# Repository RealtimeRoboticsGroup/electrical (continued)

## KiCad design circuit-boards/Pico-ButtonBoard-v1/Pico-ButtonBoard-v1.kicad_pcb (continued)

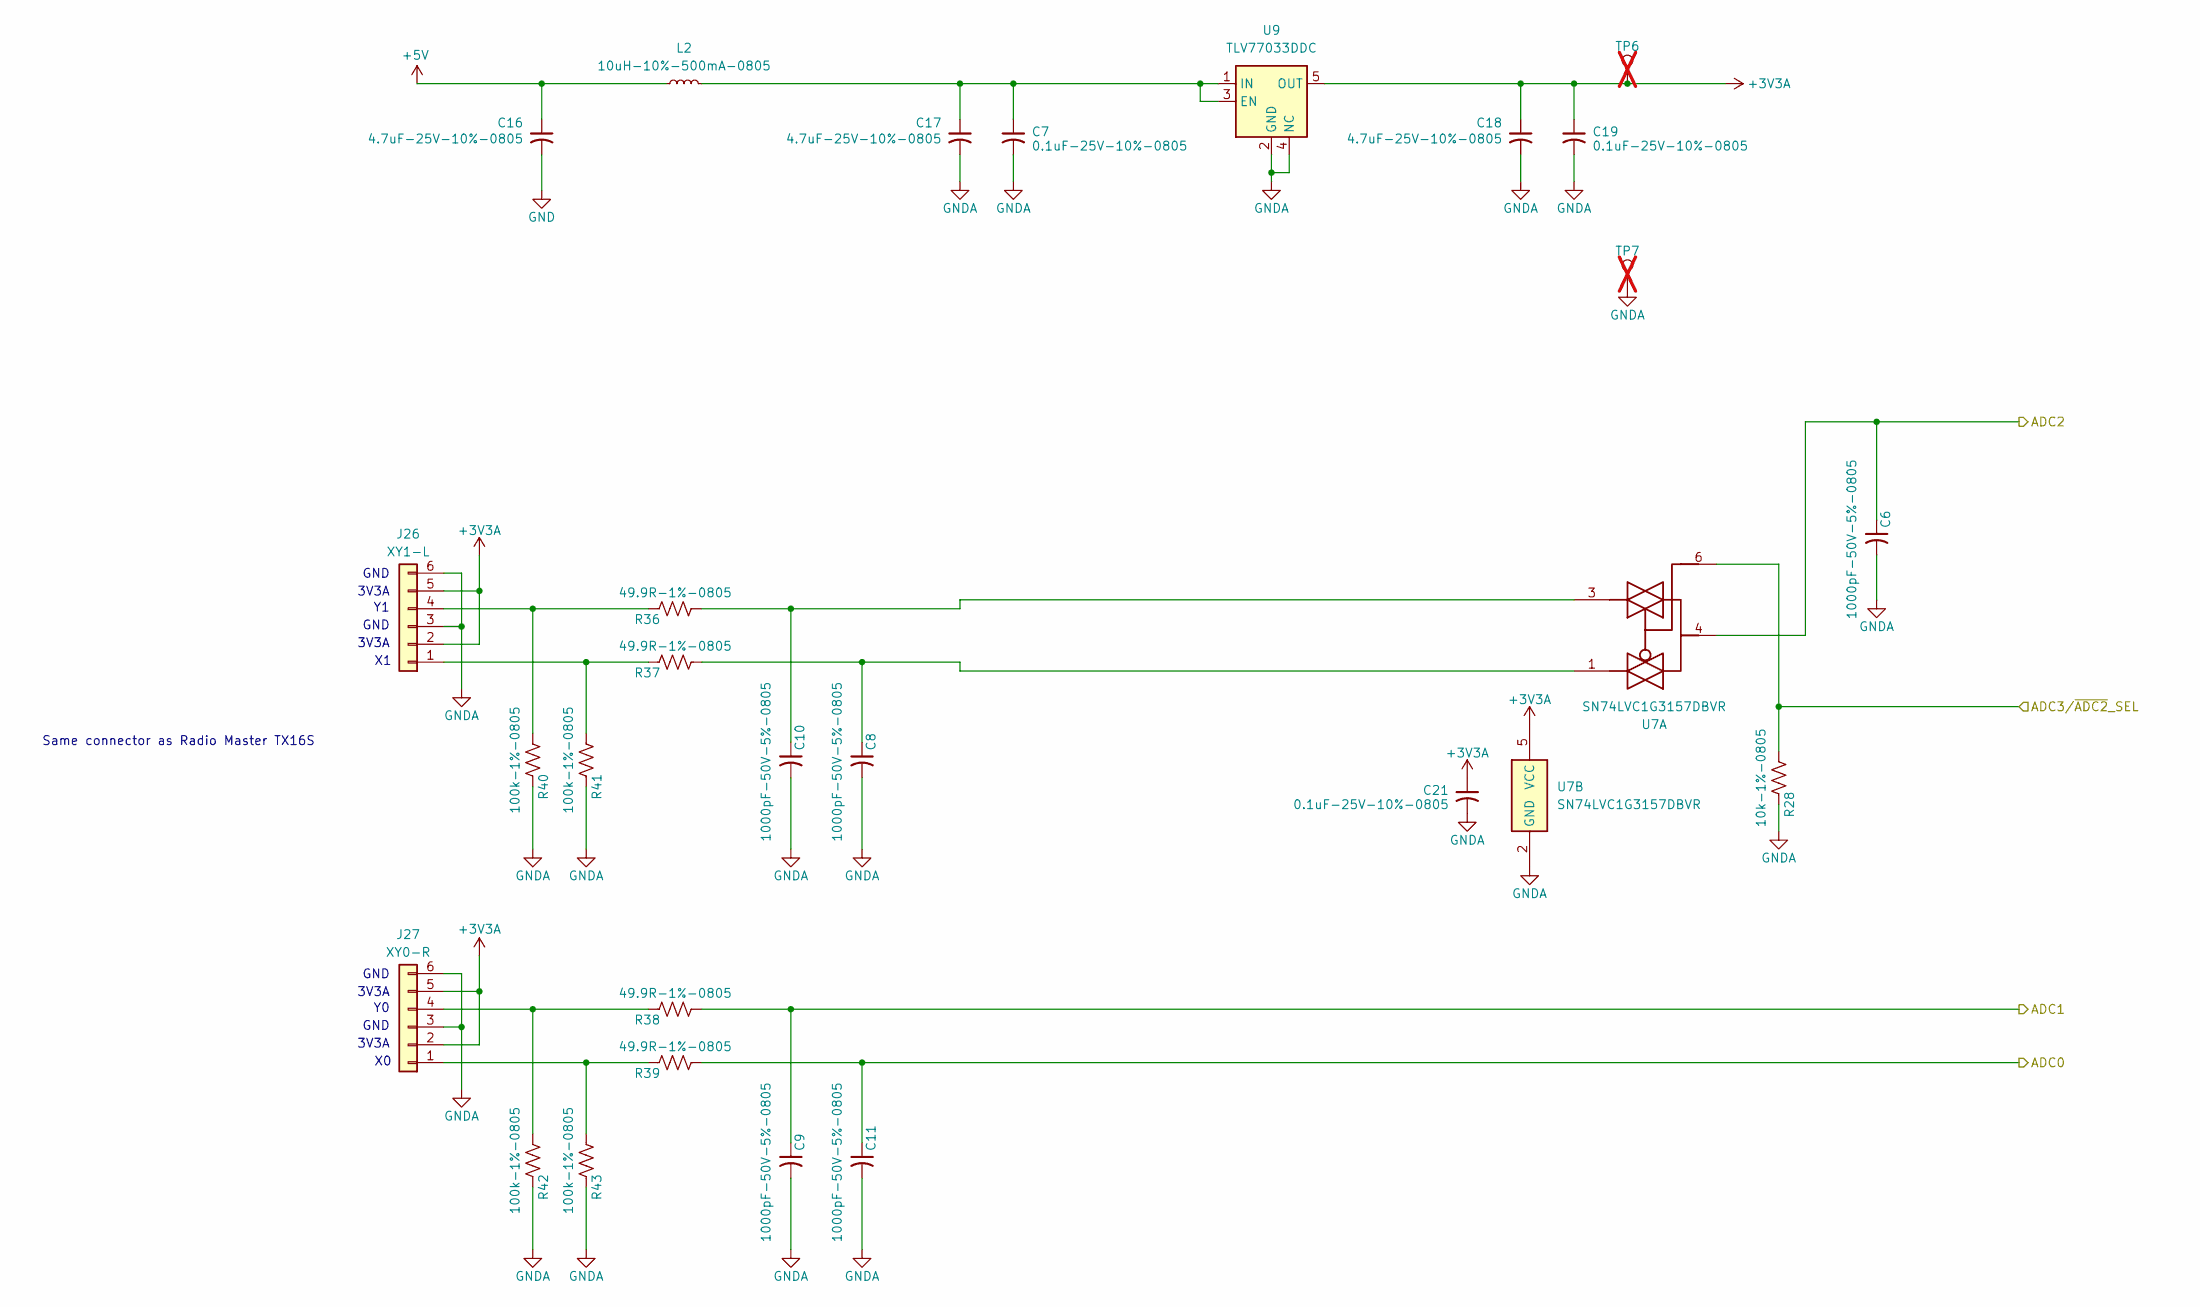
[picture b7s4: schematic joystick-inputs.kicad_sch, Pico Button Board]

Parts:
C6, C8, C9, C10, C11: 1000pF-50V-5%-0805; C_0805_2012Metric_Pad1.18x1.45mm_HandSolder; MFG P/N C0805C102J5GACTU
C7, C19, C21: 0.1uF-25V-10%-0805; C_0805_2012Metric_Pad1.18x1.45mm_HandSolder; MFG P/N 311-1141-1-ND
C16, C17, C18: 4.7uF-25V-10%-0805; C_0805_2012Metric_Pad1.18x1.45mm_HandSolder; MFG P/N C2012X5R1E475K125AB
J26: XY1-L; Molex_PicoBlade_53047-0610_1x06_P1.25mm_Vertical; MFG P/N 530470610
J27: XY0-R; Molex_PicoBlade_53047-0610_1x06_P1.25mm_Vertical; MFG P/N 530470610
L2: 10uH-10%-500mA-0805; L_0805_2012Metric_Pad1.05x1.20mm_HandSolder; MFG P/N MLZ2012N100LT000
R28: 10k-1%-0805; R_0805_2012Metric_Pad1.20x1.40mm_HandSolder; MFG P/N CRCW080510K0FKEA
R36, R37, R38, R39: 49.9R-1%-0805; R_0805_2012Metric_Pad1.20x1.40mm_HandSolder; MFG P/N RMCF0805FT49R9
R40, R41, R42, R43: 100k-1%-0805; R_0805_2012Metric_Pad1.20x1.40mm_HandSolder; MFG P/N RC0805FR-07100KL
TP6, TP7: CAN_RX; TestPoint_Keystone_5000-5004_Miniature; not fitted
U7: SN74LVC1G3157DBVR; SOT-23-6_Handsoldering; MFG P/N SN74LVC1G3157DBVR
U9: TLV77033DDC; SOT-23-5; MFG P/N TLV70033DDCR

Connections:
+3V3A: C18.1, C19.1, C21.1, J26.2, J26.5, J27.2, J27.5, TP6.1, U7.5 (VCC), U9.5 (OUT); also elsewhere on the board
+5V: C16.1, L2.1; also elsewhere on the board
/ADC3/~ADC2: R28.2, U7.6; also elsewhere on the board
/X0_ADC: C11.1, R39.1; also elsewhere on the board
/XY1_ADC: C6.1, U7.4; also elsewhere on the board
/Y0_ADC: C9.1, R38.1; also elsewhere on the board
GND: C16.2; also elsewhere on the board
GNDA: C6.2, C7.2, C8.2, C9.2, C10.2, C11.2, C17.2, C18.2, C19.2, C21.2, J26.3, J26.6, J27.3, J27.6, R28.1, R40.1, R41.1, R42.1, R43.1, TP7.1, U7.2 (GND), U9.2 (GND), U9.4 (NC); also elsewhere on the board
unnamed: C8.1, R37.1, U7.1
unnamed: C10.1, R36.1, U7.3
unnamed: J26.1, R37.2, R41.2
unnamed: J26.4, R36.2, R40.2
unnamed: J27.1, R39.2, R43.2
unnamed: J27.4, R38.2, R42.2
unnamed: C7.1, C17.1, L2.2, U9.1 (IN), U9.3 (EN)

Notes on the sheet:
3V3A
GND
Same connector as Radio Master TX16S

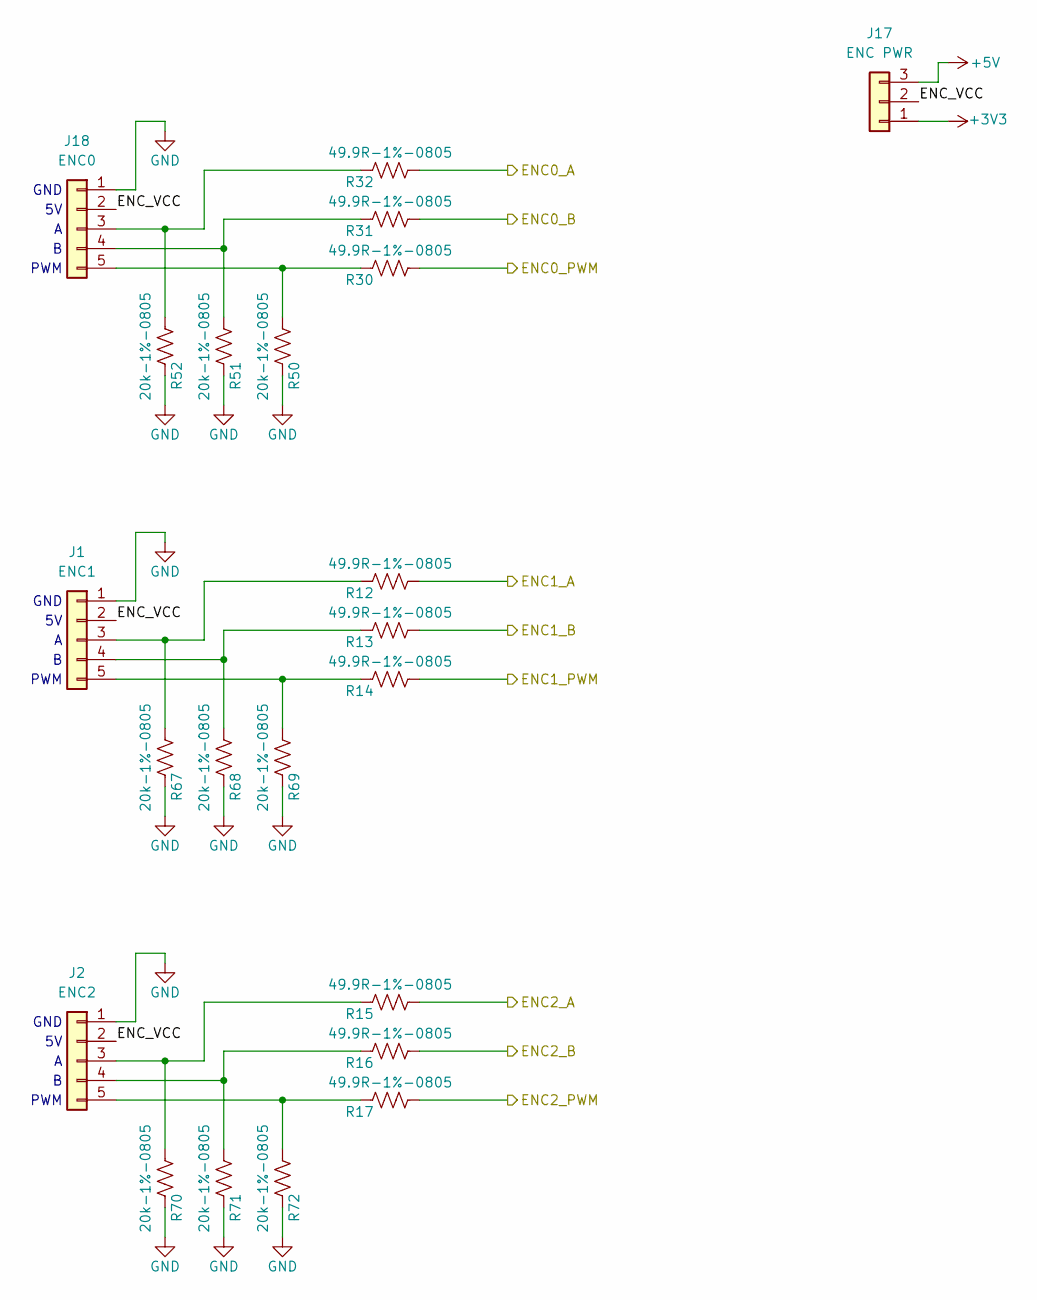
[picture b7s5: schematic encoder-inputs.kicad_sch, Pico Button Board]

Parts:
J1: ENC1; Molex-70543-0039; MFG P/N 0705430039
J2: ENC2; Molex-70543-0039; MFG P/N 0705430039
J17: ENC PWR; PinHeader_1x03_P2.54mm_Vertical
J18: ENC0; Molex-70543-0039; MFG P/N 0705430039
R12, R13, R14, R15, R16, R17, R30, R31, R32: 49.9R-1%-0805; R_0805_2012Metric_Pad1.20x1.40mm_HandSolder; MFG P/N RMCF0805FT49R9
R50, R51, R52, R67, R68, R69, R70, R71, R72: 20k-1%-0805; R_0805_2012Metric_Pad1.20x1.40mm_HandSolder; MFG P/N ERJ-6ENF2002V

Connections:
+3V3: J17.1; also elsewhere on the board
+5V: J17.3; also elsewhere on the board
/ENC0_A: R32.1; also elsewhere on the board
/ENC0_B: R31.1; also elsewhere on the board
/ENC0_PWM: R30.1; also elsewhere on the board
/ENC1_A: R12.1; also elsewhere on the board
/ENC1_B: R13.1; also elsewhere on the board
/ENC1_PWM: R14.1; also elsewhere on the board
/ENC2_A: R15.1; also elsewhere on the board
/ENC2_B: R16.1; also elsewhere on the board
/ENC2_PWM: R17.1; also elsewhere on the board
/Encoder Inputs/ENC_VCC: J1.2, J2.2, J17.2, J18.2
GND: J1.1, J2.1, J18.1, R50.1, R51.1, R52.1, R67.1, R68.1, R69.1, R70.1, R71.1, R72.1; also elsewhere on the board
unnamed: J1.3, R12.2, R67.2
unnamed: J1.4, R13.2, R68.2
unnamed: J1.5, R14.2, R69.2
unnamed: J2.3, R15.2, R70.2
unnamed: J2.4, R16.2, R71.2
unnamed: J2.5, R17.2, R72.2
unnamed: J18.3, R32.2, R52.2
unnamed: J18.4, R31.2, R51.2
unnamed: J18.5, R30.2, R50.2

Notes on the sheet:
GND
PWM

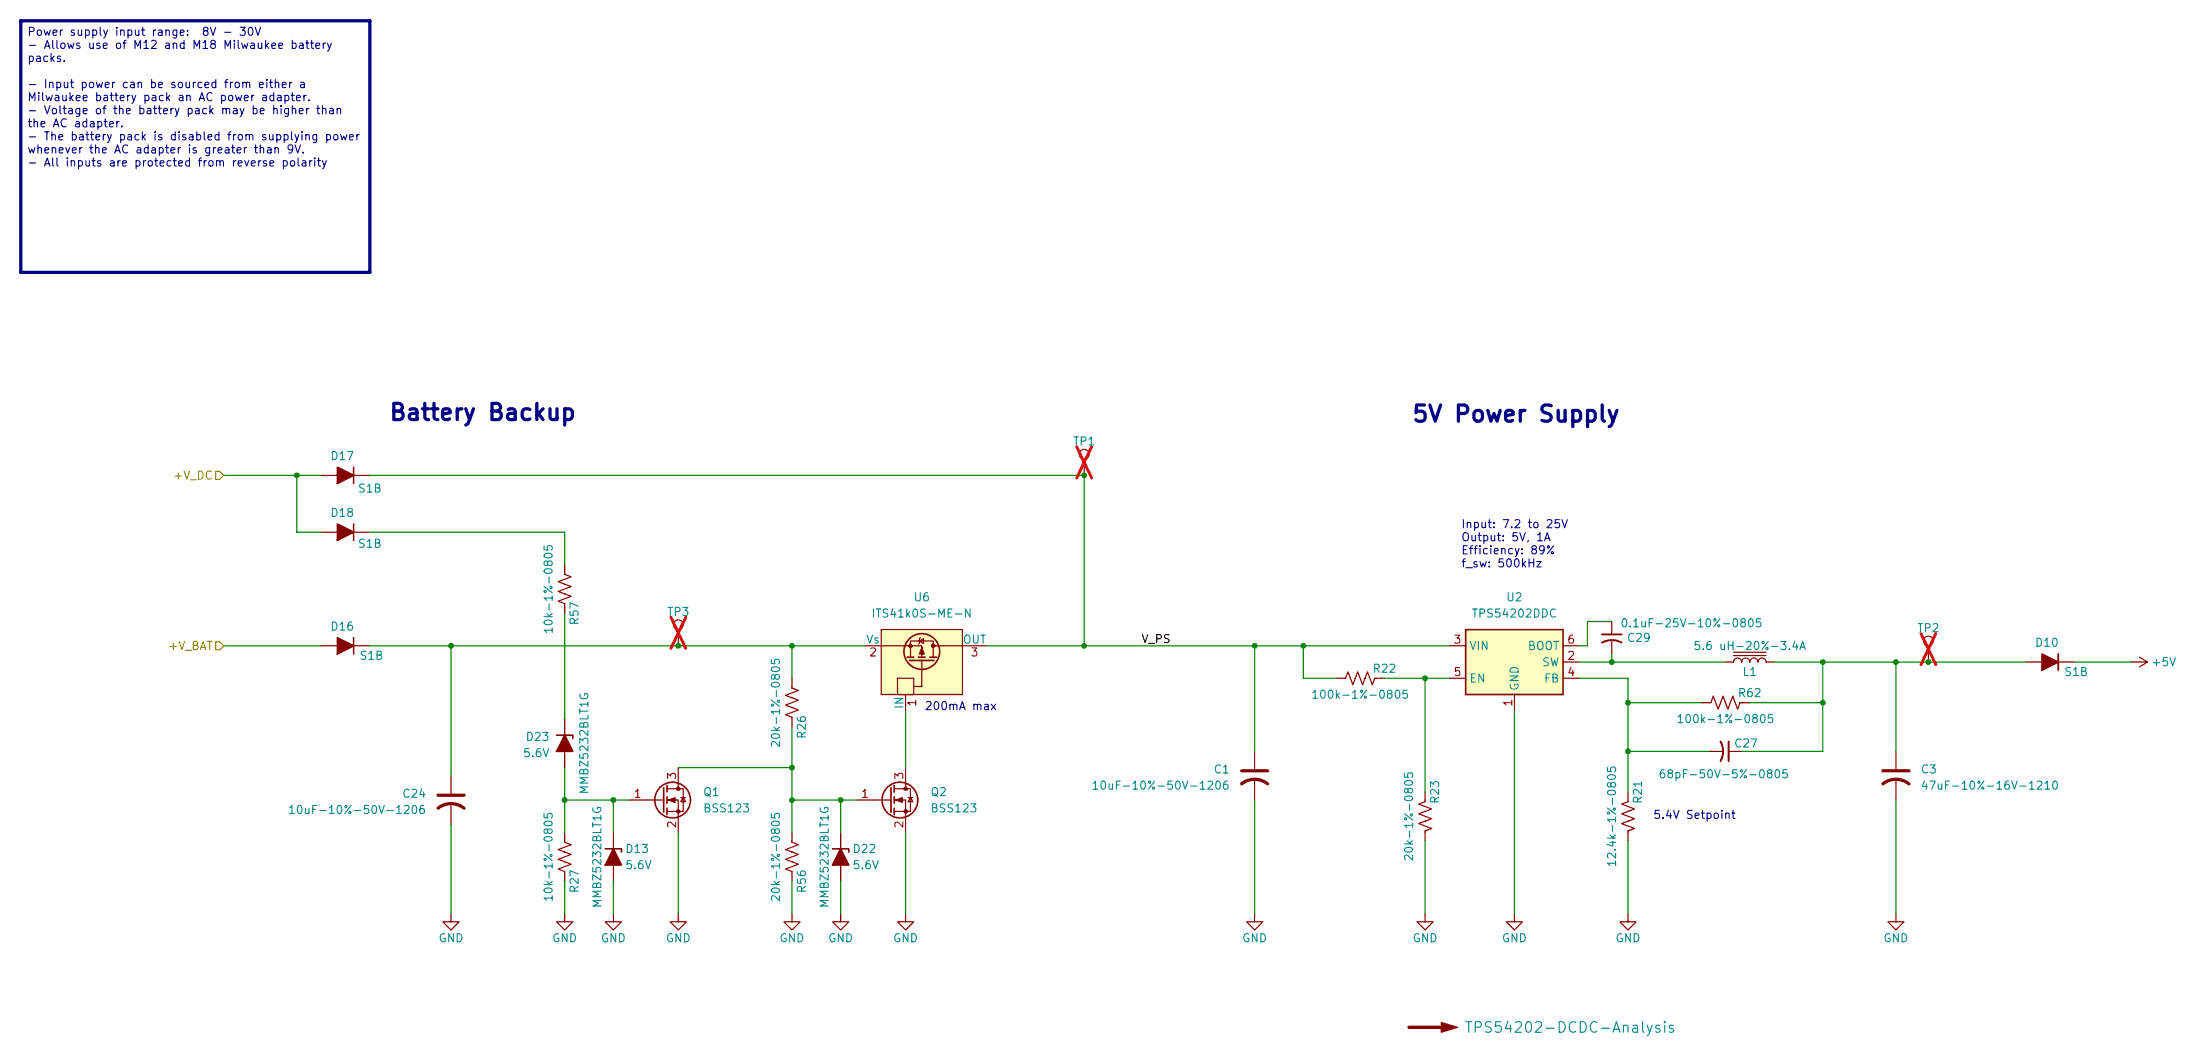
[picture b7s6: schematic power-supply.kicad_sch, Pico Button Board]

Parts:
C1, C24: 10uF-10%-50V-1206; C_1206_3216Metric_Pad1.33x1.80mm_HandSolder; MFG P/N CL31A106KBHNNNE
C3: 47uF-10%-16V-1210; C_1210_3225Metric_Pad1.33x2.70mm_HandSolder; MFG P/N CL32A476KOJNNNE
C27: 68pF-50V-5%-0805; C_0805_2012Metric_Pad1.18x1.45mm_HandSolder; MFG P/N CC0805JRNPO9BN680
C29: 0.1uF-25V-10%-0805; C_0805_2012Metric_Pad1.18x1.45mm_HandSolder; MFG P/N 311-1141-1-ND
D10, D16, D17, D18: S1B; D_SMA; MFG P/N S1B
D13, D22, D23: 5.6V; SOT-23-3; MFG P/N MMBZ5232BLT1G
L1: 5.6 uH-20%-3.4A; Cyntec-MS6-Inductor; MFG P/N VCHA042A-5R6MS6
Q1, Q2: BSS123; SOT-23-3; MFG P/N BSS123
R21: 12.4k-1%-0805; R_0805_2012Metric_Pad1.20x1.40mm_HandSolder; MFG P/N RMCF0805FT12K4
R22, R62: 100k-1%-0805; R_0805_2012Metric_Pad1.20x1.40mm_HandSolder; MFG P/N RC0805FR-07100KL
R23, R26, R56: 20k-1%-0805; R_0805_2012Metric_Pad1.20x1.40mm_HandSolder; MFG P/N ERJ-6ENF2002V
R27, R57: 10k-1%-0805; R_0805_2012Metric_Pad1.20x1.40mm_HandSolder; MFG P/N CRCW080510K0FKEA
TP1, TP2, TP3: CAN_RX; TestPoint_Keystone_5000-5004_Miniature; not fitted
U2: TPS54202DDC; SOT-23-6; MFG P/N TPS54202DDCT
U6: ITS41k0S-ME-N; SOT-223-3_TabPin2; MFG P/N ITS41K0SMENHUMA1

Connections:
+5V: D10.1 (K); also elsewhere on the board
/Power Supply/+V_BAT: D16.2 (A); also elsewhere on the board
/Power Supply/+V_DC: D17.2 (A), D18.2 (A); also elsewhere on the board
/Power Supply/V_PS: C1.1, D17.1 (K), R22.2, TP1.1, U2.3 (VIN), U6.3 (OUT)
GND: C1.2, C3.2, C24.2, D13.1 (A), D22.1 (A), Q1.2 (S), Q2.2 (S), R21.2, R23.2, R27.1, R56.1, U2.1 (GND); also elsewhere on the board
unnamed: C3.1, C27.1, D10.2 (A), L1.2, R62.1, TP2.1
unnamed: D13.3 (K), D23.1 (A), Q1.1 (G), R27.2
unnamed: C24.1, D16.1 (K), R26.2, TP3.1, U6.2 (Vs)
unnamed: D18.1 (K), R57.2
unnamed: D22.3 (K), Q1.3 (D), Q2.1 (G), R26.1, R56.2
unnamed: D23.3 (K), R57.1
unnamed: Q2.3 (D), U6.1 (IN)
unnamed: C29.1, U2.6 (BOOT)
unnamed: R22.1, R23.1, U2.5 (EN)
unnamed: C27.2, R21.1, R62.2, U2.4 (FB)
unnamed: C29.2, L1.1, U2.2 (SW)

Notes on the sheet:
Input: 7.2 to 25V Output: 5V, 1A Efficiency: 89% f_sw: 500kHz
Battery Backup
5V Power Supply
200mA max
5.4V Setpoint
Power supply input range: 8V - 30V - Allows use of M12 and M18 Milwaukee battery packs. - Input power can be sourced from either a Milwaukee battery pack an AC power adapter. - Voltage of the battery pack may be higher than the AC adapter. - The battery pack is disabled from supplying power wheneve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

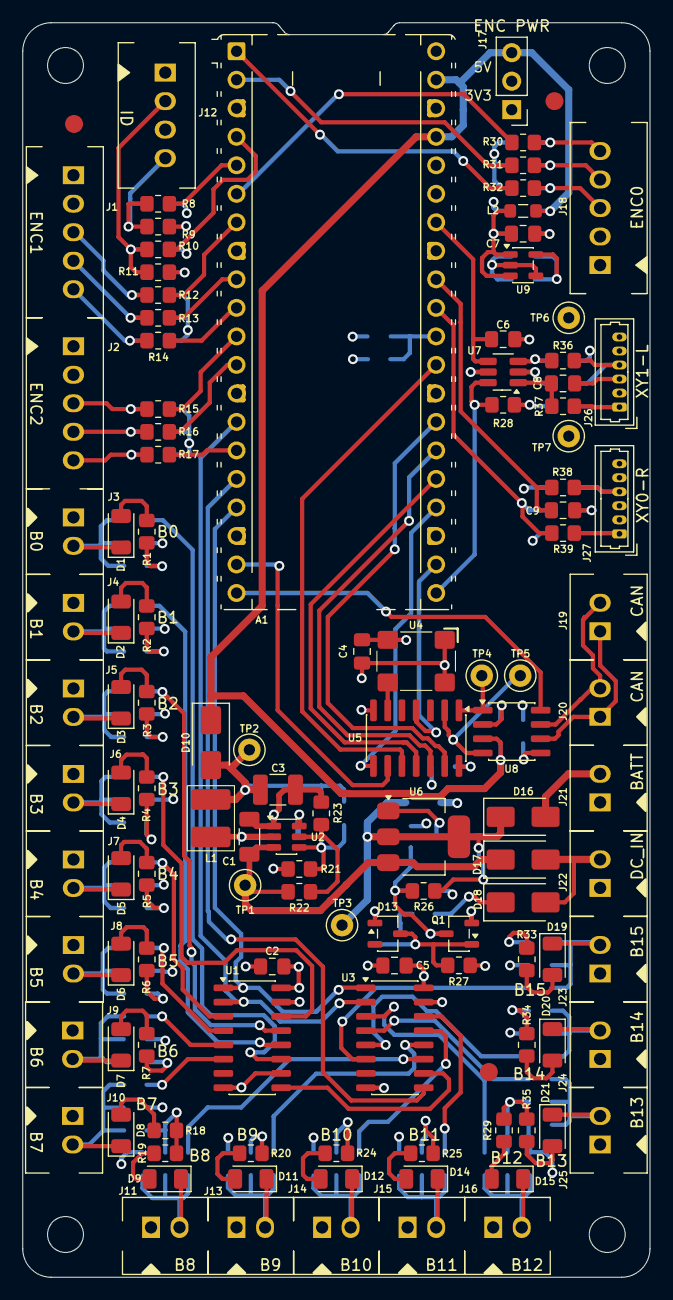
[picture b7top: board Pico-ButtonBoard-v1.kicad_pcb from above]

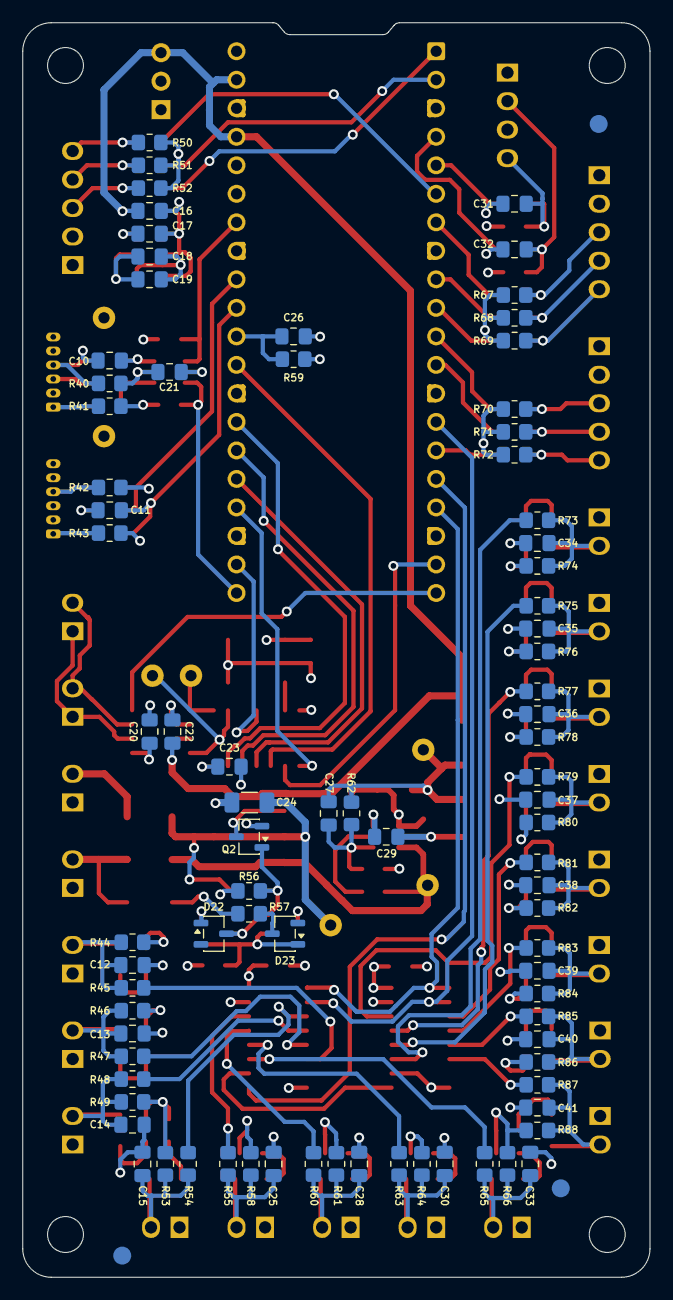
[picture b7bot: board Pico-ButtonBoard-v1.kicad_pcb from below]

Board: 4 copper layers, 55.9 x 111.8 mm, 210 parts (87 on the bottom side), 119 nets.

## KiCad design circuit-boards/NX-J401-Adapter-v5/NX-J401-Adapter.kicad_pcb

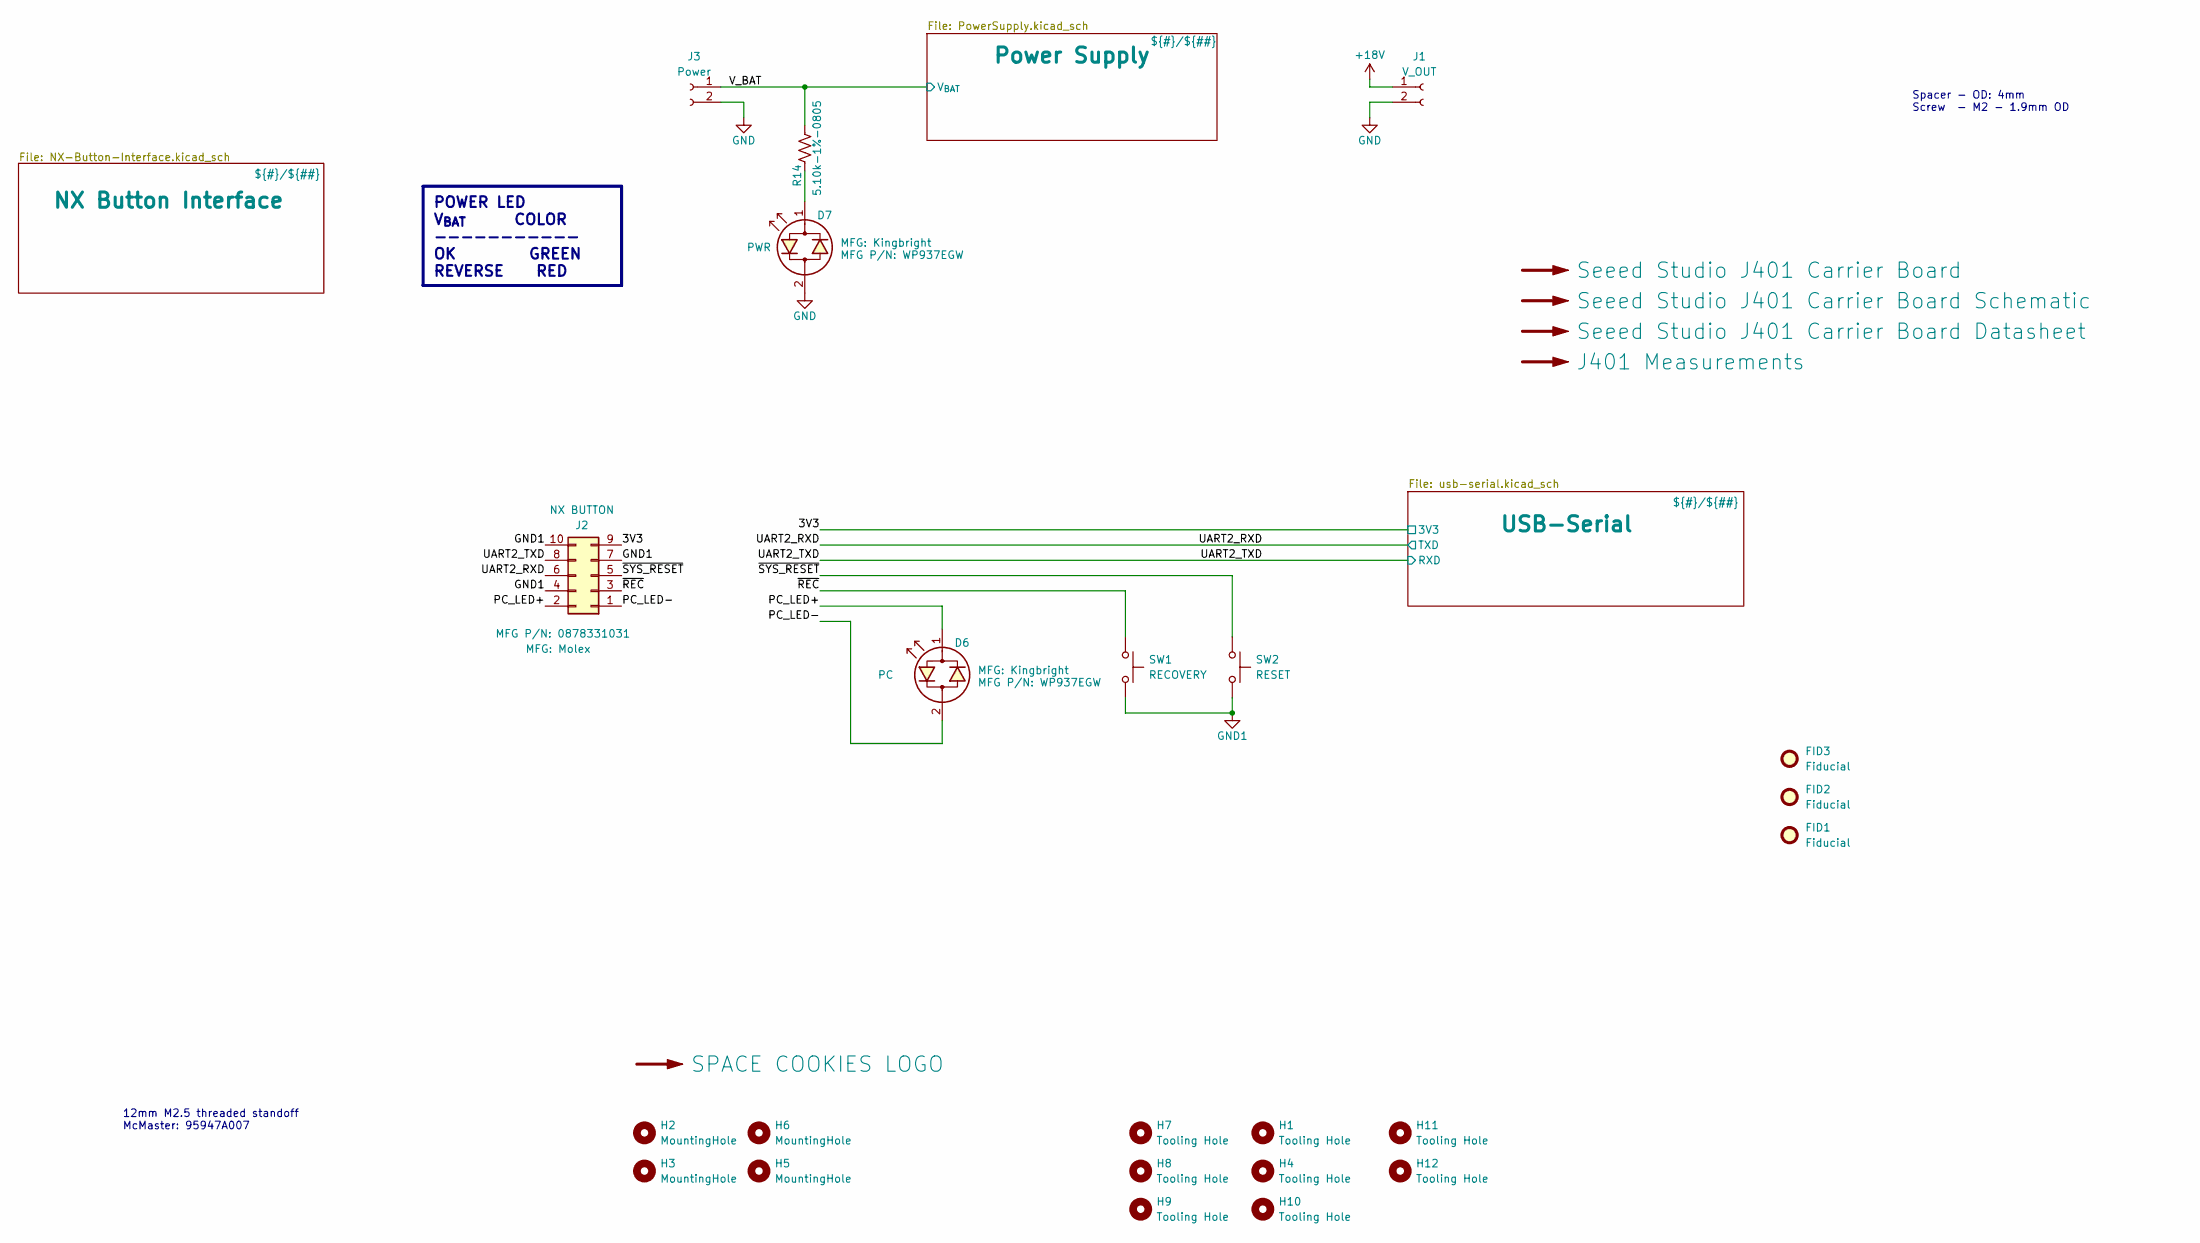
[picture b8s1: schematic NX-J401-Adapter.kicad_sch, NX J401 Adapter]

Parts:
D6: PC; LED_D3.0mm_Horizontal_O1.27mm_Z2.0mm; MFG P/N WP937EGW
D7: PWR; LED_D3.0mm_Horizontal_O1.27mm_Z2.0mm; MFG P/N WP937EGW
FID1, FID2, FID3: Fiducial; Fiducial_1.6mm_Mask3mm
H1, H4, H7, H8, H9, H10, H11, H12: Tooling Hole; ToolingHole_1.152mm
H2, H3, H5, H6: MountingHole; MountingHole_2.7mm_M2.5
J1: V_OUT; Weidmuller-1824740000; MFG P/N 1824740000
J2: NX BUTTON; Molex-0878331031; MFG P/N 0878331031
J3: Power; Weidmuller-1824740000; MFG P/N 1824740000
LOGO1: SPACE COOKIES LOGO; SPACE_COOKIES_LOGO_15mm
R14: 5.10k-1%-0805; R_0805_2012Metric; MFG P/N RC0805FR-075K1L
SW1: RECOVERY; SW_TL1105VF100Q_EWI; MFG P/N TL1105VF100Q
SW2: RESET; SW_TL1105VF100Q_EWI; MFG P/N TL1105VF100Q

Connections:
+18V: J1.1; also elsewhere on the board
/3V3: J2.9; also elsewhere on the board
/PC_LED+: D6.1 (KA), J2.2
/PC_LED-: D6.2 (AK), J2.1
/UART2_RXD: J2.6; also elsewhere on the board
/UART2_TXD: J2.8; also elsewhere on the board
/V_BAT: J3.1, R14.1; also elsewhere on the board
/~REC: J2.3, SW1.1
/~SYS_RESET: J2.5, SW2.1
GND: D7.2 (AK), J1.2, J3.2; also elsewhere on the board
GND1: J2.4, J2.7, J2.10, SW1.2, SW2.2; also elsewhere on the board
unnamed: D7.1 (KA), R14.2

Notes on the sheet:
12mm M2.5 threaded standoff McMaster: 95947A007
Spacer - OD: 4mm Screw - M2 - 1.9mm OD
POWER LED V_{BAT} COLOR ----------- OK GREEN REVERSE RED

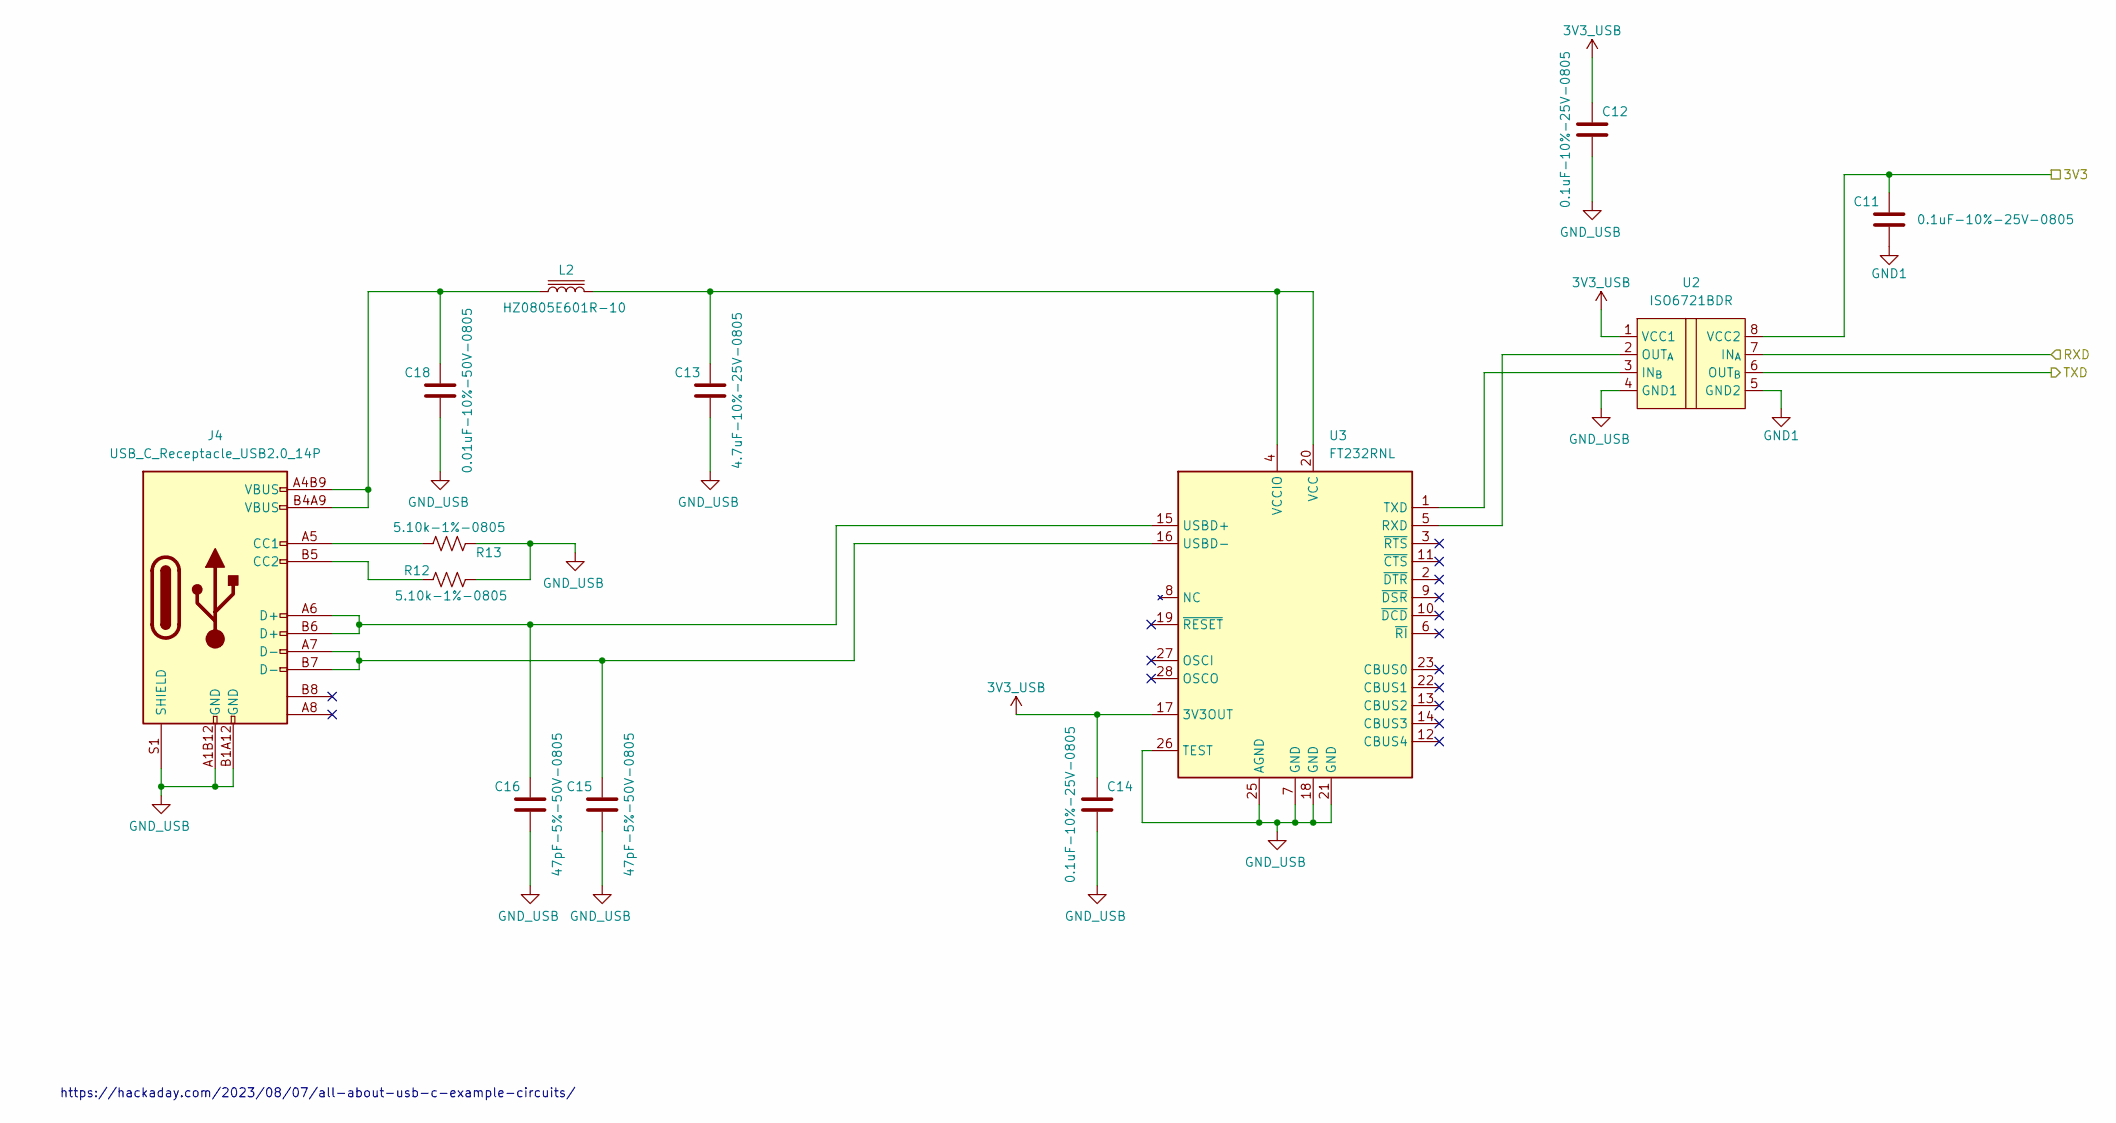
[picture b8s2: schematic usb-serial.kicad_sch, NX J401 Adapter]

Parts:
C11, C12, C14: 0.1uF-10%-25V-0805; C_0805_2012Metric; MFG P/N C0805C104K3RACTU
C13: 4.7uF-10%-25V-0805; C_0805_2012Metric; MFG P/N CL21A475KAQNNNE
C15, C16: 47pF-5%-50V-0805; C_0805_2012Metric; MFG P/N CC0805JRNPO9BN470
C18: 0.01uF-10%-50V-0805; C_0805_2012Metric; MFG P/N CL21B103KBANNNC
J4: USB_C_Receptacle_USB2.0_14P; Molex-USB-C-2171790001; MFG P/N 2171790001
L2: HZ0805E601R-10; L_0805_2012Metric; MFG P/N HZ0805E601R-10
R12, R13: 5.10k-1%-0805; R_0805_2012Metric; MFG P/N RC0805FR-075K1L
U2: ISO6721BDR; SOIC-8_3.9x4.9mm_P1.27mm; MFG P/N ISO6721BDR
U3: FT232RNL; SSOP-28_5.3x10.2mm_P0.65mm; MFG P/N FT232RNL

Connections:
3V3_USB: C12.1, C14.1, U2.1 (VCC1), U3.17 (3V3OUT)
/3V3: C11.1, U2.8 (VCC2); also elsewhere on the board
/UART2_RXD: U2.6 (OUT_{B}); also elsewhere on the board
/UART2_TXD: U2.7 (IN_{A}); also elsewhere on the board
GND1: C11.2, U2.5 (GND2); also elsewhere on the board
GND_USB: C12.2, C13.2, C14.2, C15.2, C16.2, C18.2, J4.A1B12 (GND), J4.B1A12 (GND), J4.S1 (SHIELD), R12.1, R13.1, U2.4 (GND1), U3.7 (GND), U3.18 (GND), U3.21 (GND), U3.25 (AGND), U3.26 (TEST)
unnamed: C18.1, J4.A4B9 (VBUS), J4.B4A9 (VBUS), L2.1
unnamed: J4.A5 (CC1), R13.2
unnamed: J4.B5 (CC2), R12.2
unnamed: U2.3 (IN_{B}), U3.1 (TXD)
unnamed: U2.2 (OUT_{A}), U3.5 (RXD)
unnamed: C16.1, J4.A6 (D+), J4.B6 (D+), U3.15 (USBD+)
unnamed: C15.1, J4.A7 (D-), J4.B7 (D-), U3.16 (USBD-)
unnamed: C13.1, L2.2, U3.4 (VCCIO), U3.20 (VCC)

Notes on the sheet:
https://hackaday.com/2023/08/07/all-about-usb-c-example-circuits/

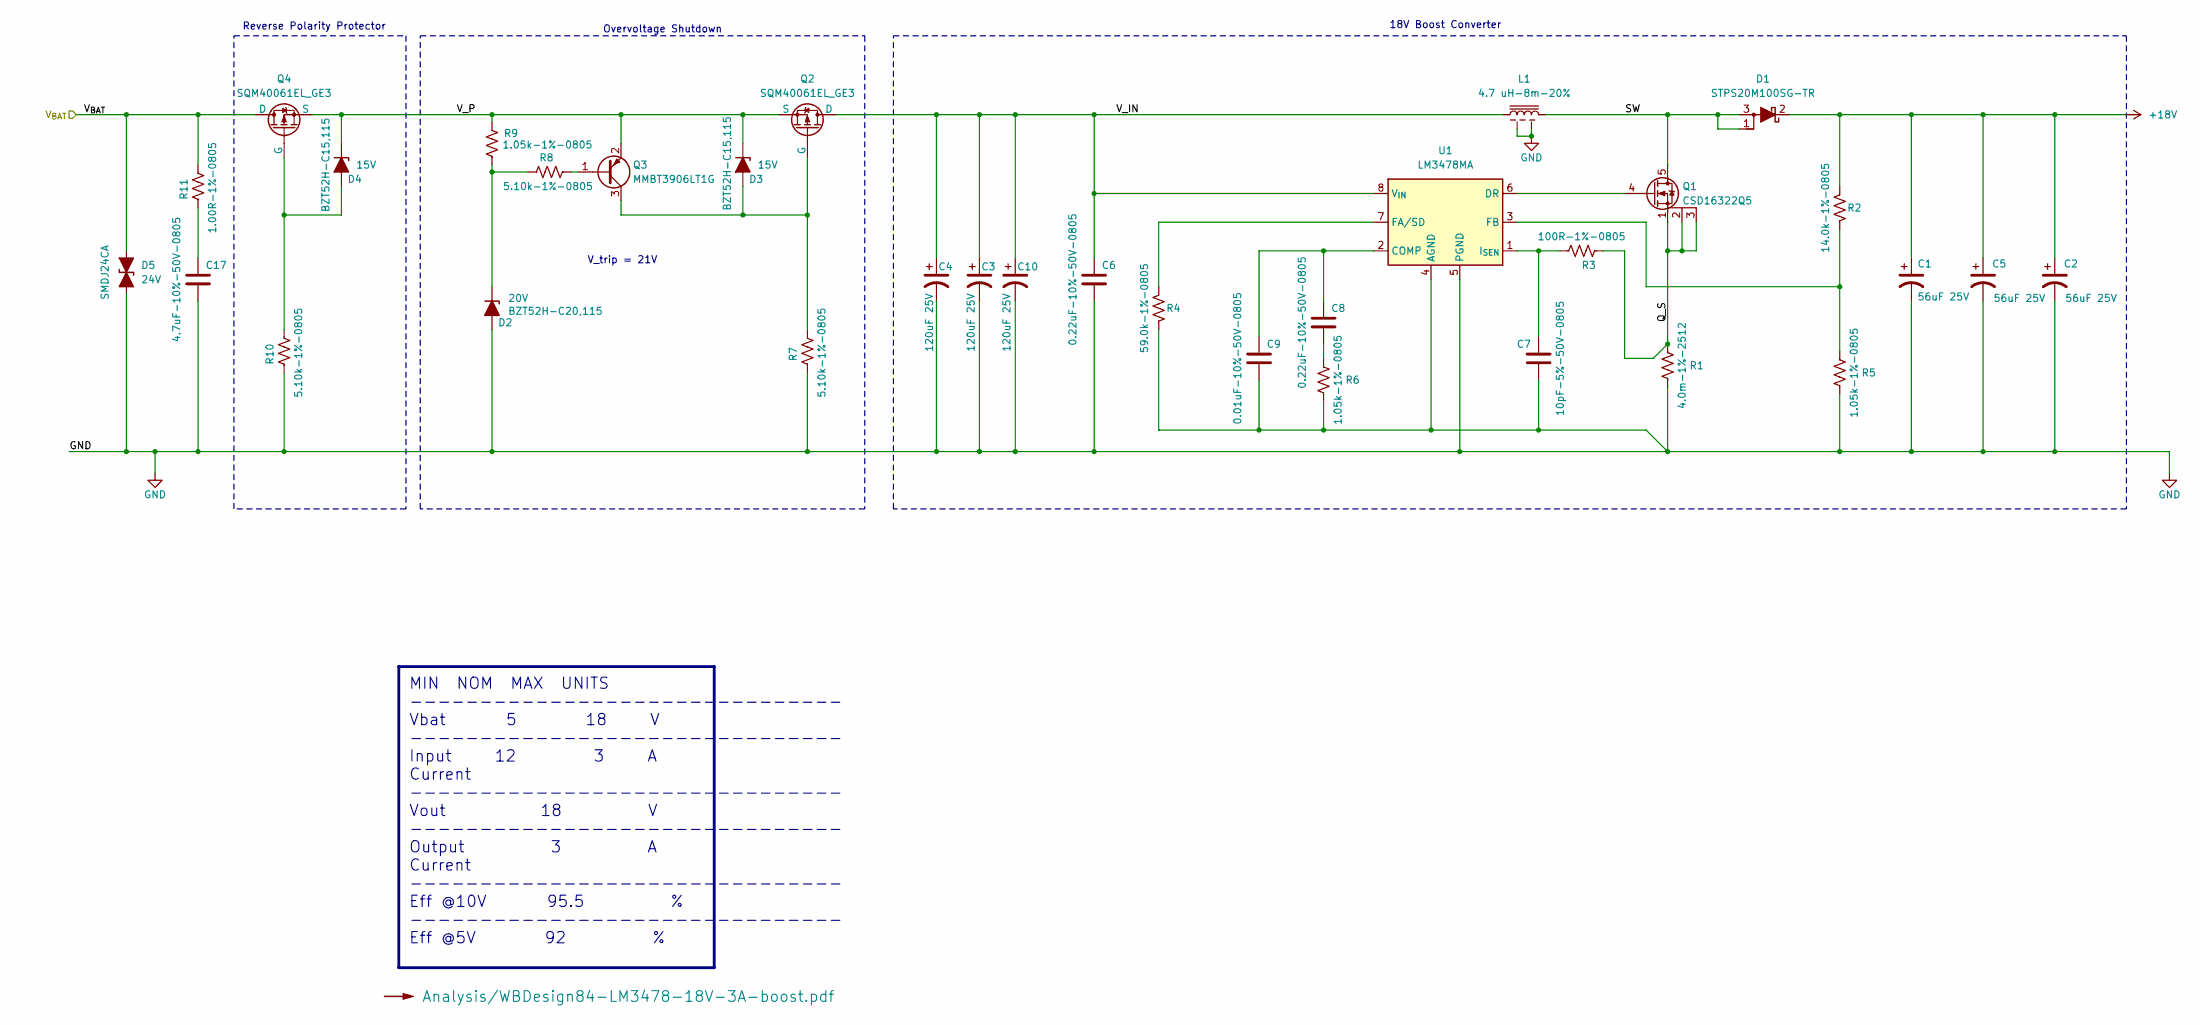
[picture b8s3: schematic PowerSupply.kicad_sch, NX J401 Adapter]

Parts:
C1, C2, C5: 56uF 25V; CP_Radial_D8.0mm_P3.50mm_H7.0mm; MFG P/N 25SEPF56M
C3, C4, C10: 120uF 25V; CP_Radial_D8.0mm_P3.50mm_H7.0mm; MFG P/N 25SEK120M
C6, C8: 0.22uF-10%-50V-0805; C_0805_2012Metric; MFG P/N C0805C224K5RAC7800
C7: 10pF-5%-50V-0805; C_0805_2012Metric; MFG P/N CL21C100CBANNNC
C9: 0.01uF-10%-50V-0805; C_0805_2012Metric; MFG P/N CL21B103KBANNNC
C17: 4.7uF-10%-50V-0805; C_0805_2012Metric; MFG P/N GRM21BR61H475KE51L
D1: STPS20M100SG-TR; TO-263-2; MFG P/N STPS20M100SG-TR
D2: 20V; D_SOD-123F; MFG P/N BZT52H-C20,115
D3, D4: 15V; D_SOD-123F; MFG P/N BZT52H-C15,115
D5: 24V; D_SMC_Littelfuse_DO-214AB; MFG P/N SMDJ24CA
L1: 4.7 uH-8m-20%; INDUCTOR_IHLE-5050FH-Vishay; MFG P/N IHLE5050FHER4R7M5A
Q1: CSD16322Q5; TI-SON5x6; MFG P/N CSD16322Q5
Q2, Q4: SQM40061EL_GE3; TO-263-2; MFG P/N SQM40061EL_GE3
Q3: MMBT3906LT1G; SOT-23; MFG P/N MMBT3906LT1G
R1: 4.0m-1%-2512; R_2512_6332Metric; MFG P/N CRE2512-FZ-R004E-3
R2: 14.0k-1%-0805; R_0805_2012Metric; MFG P/N RC0805FR-0714KL
R3: 100R-1%-0805; R_0805_2012Metric; MFG P/N RC0805FR-07100RL
R4: 59.0k-1%-0805; R_0805_2012Metric; MFG P/N RC0805FR-0759KL
R5, R6, R9: 1.05k-1%-0805; R_0805_2012Metric; MFG P/N RC0805FR-071K05L
R7, R8, R10: 5.10k-1%-0805; R_0805_2012Metric; MFG P/N RC0805FR-075K1L
R11: 1.00R-1%-0805; R_0805_2012Metric; MFG P/N CRCW08051R00FKEAHP
U1: LM3478MA; SOIC-8_3.9x4.9mm_P1.27mm; MFG P/N LM3478MAX/NOPB

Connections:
+18V: C1.1, C2.1, C5.1, D1.2 (K), R2.2; also elsewhere on the board
/Power Supply/Q_S: Q1.1 (S), Q1.2 (S), Q1.3 (S), R1.2, R3.1
/Power Supply/SW: D1.1 (A), D1.3 (A), L1.2, Q1.5 (D)
/Power Supply/V_IN: C3.1, C4.1, C6.1, C10.1, L1.1, Q2.2 (D), U1.8 (V_{IN})
/Power Supply/V_P: D3.1 (K), D4.1 (K), Q2.3 (S), Q3.2 (E), Q4.3 (S), R9.2
/V_BAT: D5.2 (A2), Q4.2 (D), R11.2; also elsewhere on the board
GND: C1.2, C2.2, C3.2, C4.2, C5.2, C6.2, C7.2, C9.2, C10.2, C17.2, D2.2 (A), D5.1 (A1), L1.3, L1.4, R1.1, R4.1, R5.1, R6.1, R7.1, R10.1, U1.4 (AGND), U1.5 (PGND); also elsewhere on the board
unnamed: C8.2, R6.2
unnamed: C17.1, R11.1
unnamed: D2.1 (K), R8.1, R9.1
unnamed: D3.2 (A), Q2.1 (G), Q3.3 (C), R7.2
unnamed: D4.2 (A), Q4.1 (G), R10.2
unnamed: Q1.4 (G), U1.6 (DR)
unnamed: Q3.1 (B), R8.2
unnamed: C8.1, C9.1, U1.2 (COMP)
unnamed: R4.2, U1.7 (FA/SD)
unnamed: R2.1, R5.2, U1.3 (FB)
unnamed: C7.1, R3.2, U1.1 (I_{SEN})

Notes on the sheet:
Reverse Polarity Protector
V_trip = 21V
18V Boost Converter
Overvoltage Shutdown
MIN NOM MAX UNITS ------------------------------- Vbat 5 18 V ------------------------------- Input 12 3 A Current ------------------------------- Vout 18 V ------------------------------- Output 3 A Current ------------------------------- Eff @10V 95.5 % ------------------------------- Eff @5V 92 %
